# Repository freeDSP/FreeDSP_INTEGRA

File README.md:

# FreeDSP_INTEGRA

An integrated four-channel 2.1MHz switching Class-D Amplifier embedded with an ADAU1466/1452 DSP processor.

Details are stated in the [wiki page](https://github.com/freeDSP/FreeDSP_INTEGRA/wiki)  

Project [Web page (Japanese)](https://cyberpithilo.web.fc2.com/audio/FreeDSP_INTEGRA/index.html)
  
DIY Audio [Forum Thread](https://www.diyaudio.com/community/threads/freedsp-integra.420623) 

# Variations  
## INTEGRA-QUAD BALANCED XLR INPUT VERSION 

## INTEGRA-QUAD Differential RCA-PIN INPUT VERSION

## Features:

            Double Differential High-Performance ADC Input Circuit
            Balanced-XLR Input  or Differential RCA-pin Analog Input
            Optical or Coaxial S/PDIF Input
            Amanero Combo384/YORK pico or XIAO RP2040 USB-Audio Input
            Raspberry-pi ZERO 2W Slot with control buttons
            TL-232R-3V3 USB-UART Cable Connection Pin-Header for Raspberry-pi
            AUX-ADC pin header
            Onboard two AUX-ADC Trimmer-POTs
            Optional Toggle Switch for DSP control
            External Front Panel Control PCB connectivity
            DC24V Single Power Supply

# Block Diagram

# Optional Board  

# Audio Performance 
ADC Distortion Performance

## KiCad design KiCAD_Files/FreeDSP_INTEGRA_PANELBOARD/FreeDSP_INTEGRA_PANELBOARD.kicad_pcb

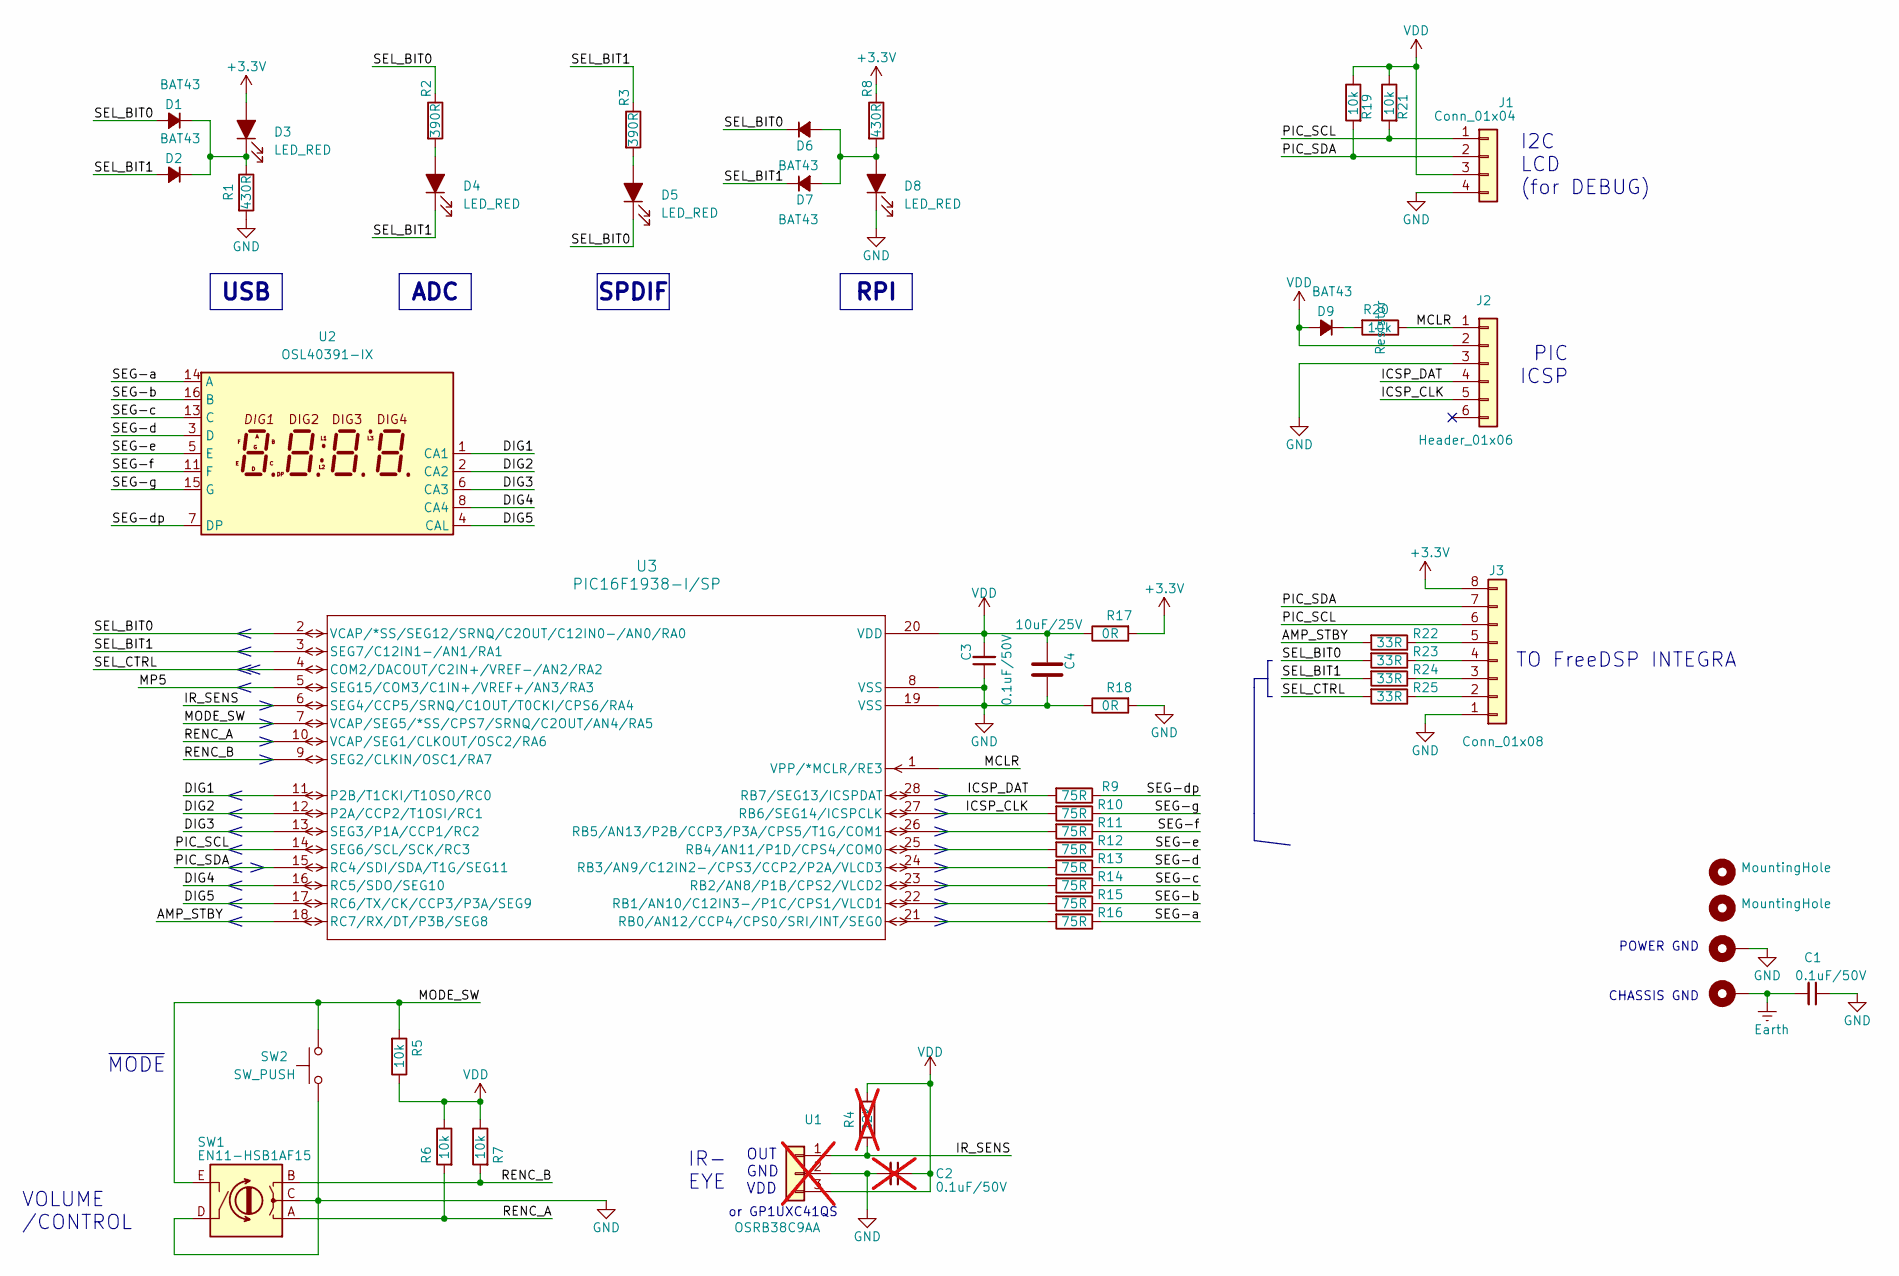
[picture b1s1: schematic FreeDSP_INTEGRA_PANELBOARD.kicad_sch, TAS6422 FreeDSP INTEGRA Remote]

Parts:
C1, C3: 0.1uF/50V; C_Disc_D4.3mm_W1.9mm_P5.00mm
C2: 0.1uF/50V; C_Disc_D4.3mm_W1.9mm_P5.00mm; not fitted
C4: 10uF/25V; C_0805_2012Metric
D1, D2, D6, D7, D9: BAT43; D_A-405_P7.62mm_Horizontal
D3, D4, D5, D8: LED_RED; LED_D3.0mm_FlatTop
HM1: MountingHole_Pad_via; MountingHole_3.2mm_M3_ISO7380_Pad_TopBottom
J1: Conn_01x04; PinHeader_1x04_P2.54mm_Vertical
J2: Header_01x06; PinHeader_1x06_P2.54mm_Vertical
J3: Conn_01x08; PinHeader_1x08_P2.54mm_Vertical
MH1, MH2: MountingHole; MountingHole_3.2mm_M3_DIN965_Pad_TopBottom
MH3: M3; MountingHole_3.2mm_M3_Pad_Via
R1, R8: 430R; R_Axial_DIN0204_L3.6mm_D1.6mm_P5.08mm_Horizontal
R2, R3: 390R; R_Axial_DIN0204_L3.6mm_D1.6mm_P5.08mm_Horizontal
R4: 22k; R_Axial_DIN0204_L3.6mm_D1.6mm_P5.08mm_Horizontal; not fitted
R5, R6, R7, R19, R20, R21: 10k; R_Axial_DIN0204_L3.6mm_D1.6mm_P5.08mm_Horizontal
R9, R10, R11, R12, R13, R14, R15, R16: 75R; R_Axial_DIN0204_L3.6mm_D1.6mm_P5.08mm_Horizontal
R17, R18: 0R; R_Axial_DIN0204_L3.6mm_D1.6mm_P5.08mm_Horizontal
R22, R23, R24, R25: 33R; R_Axial_DIN0204_L3.6mm_D1.6mm_P5.08mm_Horizontal
SW1: EN11-HSB1AF15; RotaryEncoder_TT-Ele_EN11-HSB1AF15
SW2: SW_PUSH; SW_PUSH_6mm_H4.3mm
U1: OSRB38C9AA; IR_Receiver_TSOP38238; not fitted
U2: OSL40391-IX; LTC-4627Jx
U3: PIC16F1938-I/SP; PIC16F1938-X&slash_SP_MCH(Socket)

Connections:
+3.3V: D3.2 (A), J3.8, R8.1, R17.2
/AMP_STBY: R22.2, U3.18 (RC7/RX/DT/P3B/SEG8)
/DIG1: U2.1 (CA1), U3.11 (P2B/T1CKI/T1OSO/RC0)
/DIG2: U2.2 (CA2), U3.12 (P2A/CCP2/T1OSI/RC1)
/DIG3: U2.6 (CA3), U3.13 (SEG3/P1A/CCP1/RC2)
/DIG4: U2.8 (CA4), U3.16 (RC5/SDO/SEG10)
/DIG5: U2.4 (CAL), U3.17 (RC6/TX/CK/CCP3/P3A/SEG9)
/ICSP_CLK: J2.5, R10.2, U3.27 (RB6/SEG14/ICSPCLK)
/ICSP_DAT: J2.4, R9.2, U3.28 (RB7/SEG13/ICSPDAT)
/IR_SENS: R4.2, U1.1, U3.6 (SEG4/CCP5/SRNQ/C1OUT/T0CKI/CPS6/RA4)
/MCLR: J2.1, R20.1, U3.1 (VPP/*MCLR/RE3)
/MODE_SW: R5.2, SW1.E, SW2.2, U3.7 (VCAP/SEG5/*SS/CPS7/SRNQ/C2OUT/AN4/RA5)
/MP5: U3.5 (SEG15/COM3/C1IN+/VREF+/AN3/RA3)
/PIC_SCL: J1.1, J3.6, R21.2, U3.14 (SEG6/SCL/SCK/RC3)
/PIC_SDA: J1.2, J3.7, R19.2, U3.15 (RC4/SDI/SDA/T1G/SEG11)
/RENC_A: R6.2, SW1.A, U3.10 (VCAP/SEG1/CLKOUT/OSC2/RA6)
/RENC_B: R7.2, SW1.B, U3.9 (SEG2/CLKIN/OSC1/RA7)
/SEG-a: R16.1, U2.14 (A)
/SEG-b: R15.1, U2.16 (B)
/SEG-c: R14.1, U2.13 (C)
/SEG-d: R13.1, U2.3 (D)
/SEG-dp: R9.1, U2.7 (DP)
/SEG-e: R12.1, U2.5 (E)
/SEG-f: R11.1, U2.11 (F)
/SEG-g: R10.1, U2.15 (G)
/SEL_BIT0: D1.2 (A), D5.1 (K), D6.1 (K), R2.1, R23.2, U3.2 (VCAP/*SS/SEG12/SRNQ/C2OUT/C12IN0-/AN0/R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)
/SEL_BIT1: D2.2 (A), D4.1 (K), D7.1 (K), R3.1, R24.2, U3.3 (SEG7/C12IN1-/AN1/RA1)
/SEL_CTRL: R25.2, U3.4 (COM2/DACOUT/C2IN+/VREF-/AN2/RA2)
Earth: C1.2, MH3.1
GND: C1.1, C2.2, C3.1, C4.2, D8.1 (K), HM1.1, J1.4, J2.3, J3.1, R1.2, R18.1, R18.2, SW1.C, SW1.D, SW2.1, U1.2, U3.8 (VSS), U3.19 (VSS)
unnamed: D1.1 (K), D2.1 (K), D3.1 (K), R1.1
unnamed: D4.2 (A), R2.2
unnamed: D5.2 (A), R3.2
unnamed: D6.2 (A), D7.2 (A), D8.2 (A), R8.2
unnamed: D9.1 (K), R20.2
unnamed: J3.2, R25.1
unnamed: J3.3, R24.1
unnamed: J3.4, R23.1
unnamed: J3.5, R22.1
unnamed: R16.2, U3.21 (RB0/AN12/CCP4/CPS0/SRI/INT/SEG0)
unnamed: R15.2, U3.22 (RB1/AN10/C12IN3-/P1C/CPS1/VLCD1)
unnamed: R14.2, U3.23 (RB2/AN8/P1B/CPS2/VLCD2)
unnamed: R13.2, U3.24 (RB3/AN9/C12IN2-/CPS3/CCP2/P2A/VLCD3)
unnamed: R12.2, U3.25 (RB4/AN11/P1D/CPS4/COM0)
unnamed: R11.2, U3.26 (RB5/AN13/P2B/CCP3/P3A/CPS5/T1G/COM1)
VDD: C2.1, C3.2, C4.1, D9.2 (A), J1.3, J2.2, R4.1, R5.1, R6.1, R7.1, R17.1, R19.1, R21.1, U1.3, U3.20 (VDD)

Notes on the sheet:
~{MODE}
OUT GND VDD
IR- EYE
CHASSIS GND
PIC ICSP
I2C LCD (for DEBUG)
TO FreeDSP INTEGRA
VOLUME /CONTROL
POWER GND
or GP1UXC41QS
USB
SPDIF
ADC
RPI

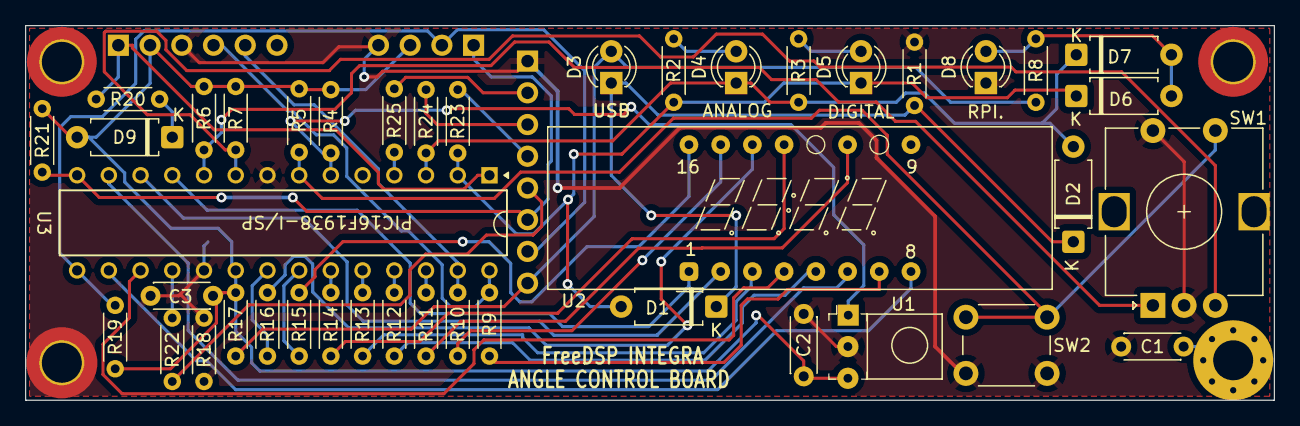
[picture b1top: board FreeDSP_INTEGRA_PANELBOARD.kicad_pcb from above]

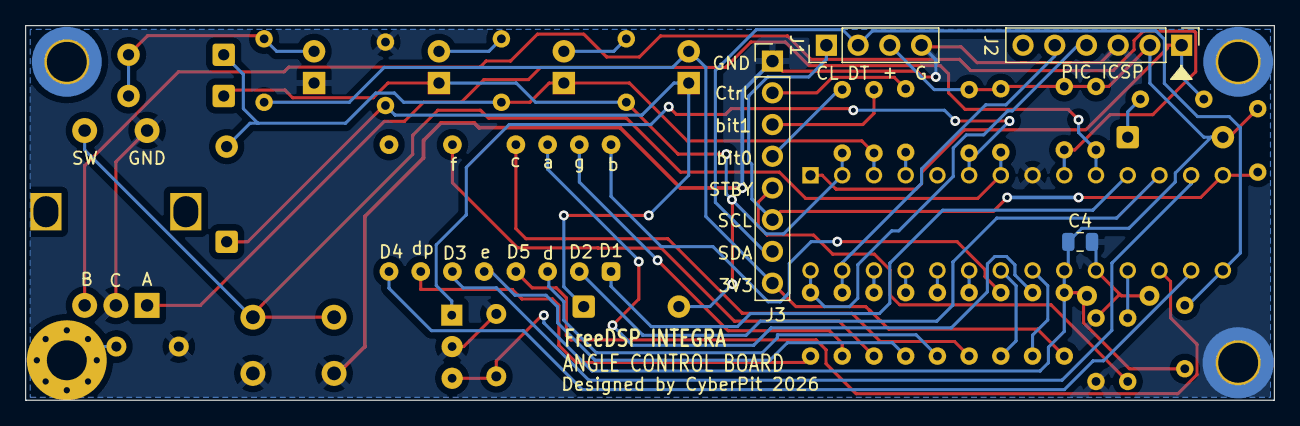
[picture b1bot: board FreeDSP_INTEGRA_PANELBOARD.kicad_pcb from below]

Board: 2 copper layers, 100.0 x 30.0 mm, 50 parts (4 on the bottom side), 45 nets.

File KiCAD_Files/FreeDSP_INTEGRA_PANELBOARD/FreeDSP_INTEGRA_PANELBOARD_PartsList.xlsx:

FreeUSB INTEGRA Panel Board Bill of Materials
Reference | Value | JLPCB# | Footprint | Datasheet
C1 | 0.1uF/50V | C14663 | Capacitor_THT:C_Disc_D4.3mm_W1.9mm_P5.00mm | ~
C2 | 0.1uF/50V | C28233 | Capacitor_THT:C_Disc_D4.3mm_W1.9mm_P5.00mm | ~
C3 | 0.1uF/50V | C28233 | Capacitor_THT:C_Disc_D4.3mm_W1.9mm_P5.00mm | ~
C4 | 10uF/25V | C45783 | Capacitor_SMD:C_0805_2012Metric | ~
D1,D2,D6,D7,D9 | BAT43 | C81598 | Diode_THT:D_A-405_P7.62mm_Horizontal | https://akizukidenshi.com/catalog/g/g113907/
D3,D4,D5,D8 | LED_RED |  | LED_THT:LED_D3.0mm_FlatTop | https://akizukidenshi.com/catalog/g/g111577/
HM1 | MountingHole_Pad_via | - | MountingHole:MountingHole_3.2mm_M3_ISO7380_Pad_TopBottom | ~
J1 | Conn_01x04 | NOP | Connector_PinHeader_2.54mm:PinHeader_1x04_P2.54mm_Vertical | https://akizukidenshi.com/catalog/g/g100167/
J2 | Header_01x06 | HAND | Connector_PinHeader_2.54mm:PinHeader_1x06_P2.54mm_Vertical
J3 | Conn_01x08 | HAND | Connector_PinHeader_2.54mm:PinHeader_1x08_P2.54mm_Vertical
MH1,MH2 | MountingHole | - | MountingHole:MountingHole_3.2mm_M3_DIN965_Pad_TopBottom | ~
MH3 | M3 | - | MountingHole:MountingHole_3.2mm_M3_Pad_Via | ~
R1,R8 | 1k |  | Resistor_THT:R_Axial_DIN0204_L3.6mm_D1.6mm_P5.08mm_Horizontal | Through-hole Lead Type Carbon Resistor 1/6W (5mm pitch)
R2,R3 | 390R |  | Resistor_THT:R_Axial_DIN0204_L3.6mm_D1.6mm_P5.08mm_Horizontal | Through-hole Lead Type Carbon Resistor 1/6W (5mm pitch)
R4 | 22k | C31850 | Resistor_THT:R_Axial_DIN0204_L3.6mm_D1.6mm_P5.08mm_Horizontal | Through-hole Lead Type Carbon Resistor 1/6W (5mm pitch)
R5,R6,R7,R19,R20,R21 | 10k | C25804 | Resistor_THT:R_Axial_DIN0204_L3.6mm_D1.6mm_P5.08mm_Horizontal | Through-hole Lead Type Carbon Resistor 1/6W (5mm pitch)
R9,R10,R11,R12,R13,R14,R15,R16 | 75R | C4275 | Resistor_THT:R_Axial_DIN0204_L3.6mm_D1.6mm_P5.08mm_Horizontal | Through-hole Lead Type Carbon Resistor 1/6W (5mm pitch)
R17,R18 | 0R | C21189 | Resistor_THT:R_Axial_DIN0204_L3.6mm_D1.6mm_P5.08mm_Horizontal | Through-hole Lead Type Carbon Resistor 1/6W (5mm pitch)
R22,R23,R24,R25 | 33R | C23140 | Resistor_THT:R_Axial_DIN0204_L3.6mm_D1.6mm_P5.08mm_Horizontal | Through-hole Lead Type Carbon Resistor 1/6W (5mm pitch)
SW1 | EN11-HSB1AF15 | HAND | Myfootprints:RotaryEncoder_TT-Ele_EN11-HSB1AF15 | https://akizukidenshi.com/catalog/g/g106357/ https://ja.aliexpress.com/item/100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
SW2 | SW_PUSH | HAND | Button_Switch_THT:SW_PUSH_6mm_H4.3mm | https://akizukidenshi.com/catalog/g/g117166/
U1 | OSRB38C9AA | NOP | digikey-footprints:IR_Receiver_TSOP38238 | NOPOP, Not Supported
U2 | OSL40391-IX | HAND | Display_7Segment:LTC-4627Jx (Anode Common) | http://optoelectronics.liteon.com/upload/download/DS30-2001-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 …
U3 | PIC16F1938-I/SP | HAND | Myfootprints:PIC16F1938-X&slash_SP_MCH(Socket) | PIC16F1938-I/SP
W1 | 8P Female-Female Cable | - | Jumper Cable | https://akizukidenshi.com/catalog/g/g115868/

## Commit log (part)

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2026-04-28 Initial Release
2026-04-28 Low cost AK5552 version
2026-04-28 PIC16F1938_SourceCode
2026-05-01 Add files via upload
    MPLABX 6.3 Project for PIC16F1938
2026-05-03 Add files via upload
    Fix some values.
2026-05-05 Parts value changed
2026-05-08 Fixed display issues
2026-05-09 Fixed missing "-" issue
2026-05-14 Fixed channel-1 voulume uncontrol issue.
2026-05-14 Variable Crossover frequency LR48 2way Amp
2026-05-20 Template project for programming start point.
2026-06-09 2way Multi-Amp Project. Variable Crossover Freq.
2026-06-09 ADAU1452 version Project
